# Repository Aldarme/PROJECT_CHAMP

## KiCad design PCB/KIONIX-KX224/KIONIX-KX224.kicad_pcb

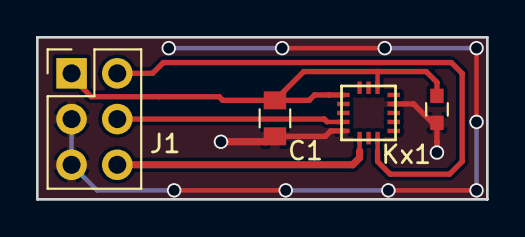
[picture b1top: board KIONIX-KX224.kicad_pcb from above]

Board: 2 copper layers, 25.0 x 9.0 mm, 4 parts (0 on the bottom side), 5 nets.

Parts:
C1: 100nF; C_0805
C2: 100nF; C_0603
J1: Conn_02x03_Odd_Even; Pin_Header_Straight_2x03_Pitch2.54mm
Kx1: KX224

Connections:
/CS/SCL: J1.2, Kx1.8
/Miso/Mosi: J1.6, Kx1.6
/SCLK: J1.4, Kx1.4
/VDD: C1.1, C2.1, J1.1, Kx1.1, Kx1.14
GNDREF: C1.2, C2.2, J1.3, J1.5, Kx1.5, Kx1.12

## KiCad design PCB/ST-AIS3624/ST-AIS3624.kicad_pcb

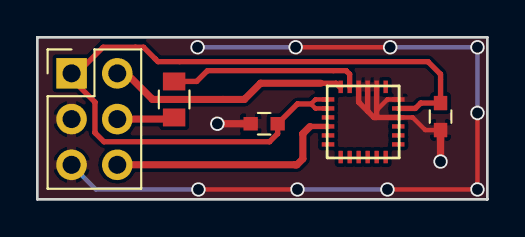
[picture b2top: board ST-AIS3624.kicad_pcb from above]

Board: 2 copper layers, 25.0 x 9.0 mm, 5 parts (0 on the bottom side), 6 nets.

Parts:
AIS36241: AIS3624DQTR; ADIS3624DQ
C1: 100nF; C_0603
C2: 10uF; C_0603
J1: Conn_02x03_Odd_Even; Pin_Header_Straight_2x03_Pitch2.54mm
JP2: Jumper; C_0805

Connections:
/CS/SCL: AIS36241.12, J1.2
/Miso/Mosi: AIS36241.16, J1.6
/SCLK: AIS36241.11, JP2.2
/VDD: AIS36241.5, AIS36241.13, AIS36241.14, C1.1, C2.1, J1.1
GNDREF: AIS36241.4, AIS36241.6, AIS36241.8, AIS36241.9, AIS36241.10, C1.2, C2.2, J1.3, J1.5
unnamed: J1.4, JP2.1

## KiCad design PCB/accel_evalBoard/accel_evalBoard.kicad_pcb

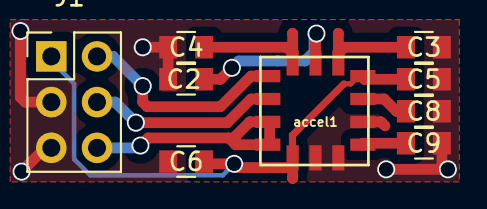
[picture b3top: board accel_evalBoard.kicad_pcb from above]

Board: 2 copper layers, 9 parts (0 on the bottom side), 10 nets.

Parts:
C2, C3, C4, C5, C6, C8, C9: 0.1uF; C_0805
J1: Conn_02x03_Odd_Even; Pin_Header_Straight_2x03_Pitch2.54mm
accel1: ADXL355

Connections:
GNDREF: C2.2, C3.2, C4.2, C5.2, C6.1, C8.1, C9.1, J1.3, J1.5, accel1.6, accel1.7, accel1.9
unnamed: C2.1, accel1.13
unnamed: C3.1, accel1.12
unnamed: C4.1, accel1.14
unnamed: C8.2, accel1.10
unnamed: C9.2, accel1.8
unnamed: J1.2, accel1.1
unnamed: J1.4, accel1.2
unnamed: J1.6, accel1.3, accel1.4
VDD: C5.1, C6.2, J1.1, accel1.5, accel1.11

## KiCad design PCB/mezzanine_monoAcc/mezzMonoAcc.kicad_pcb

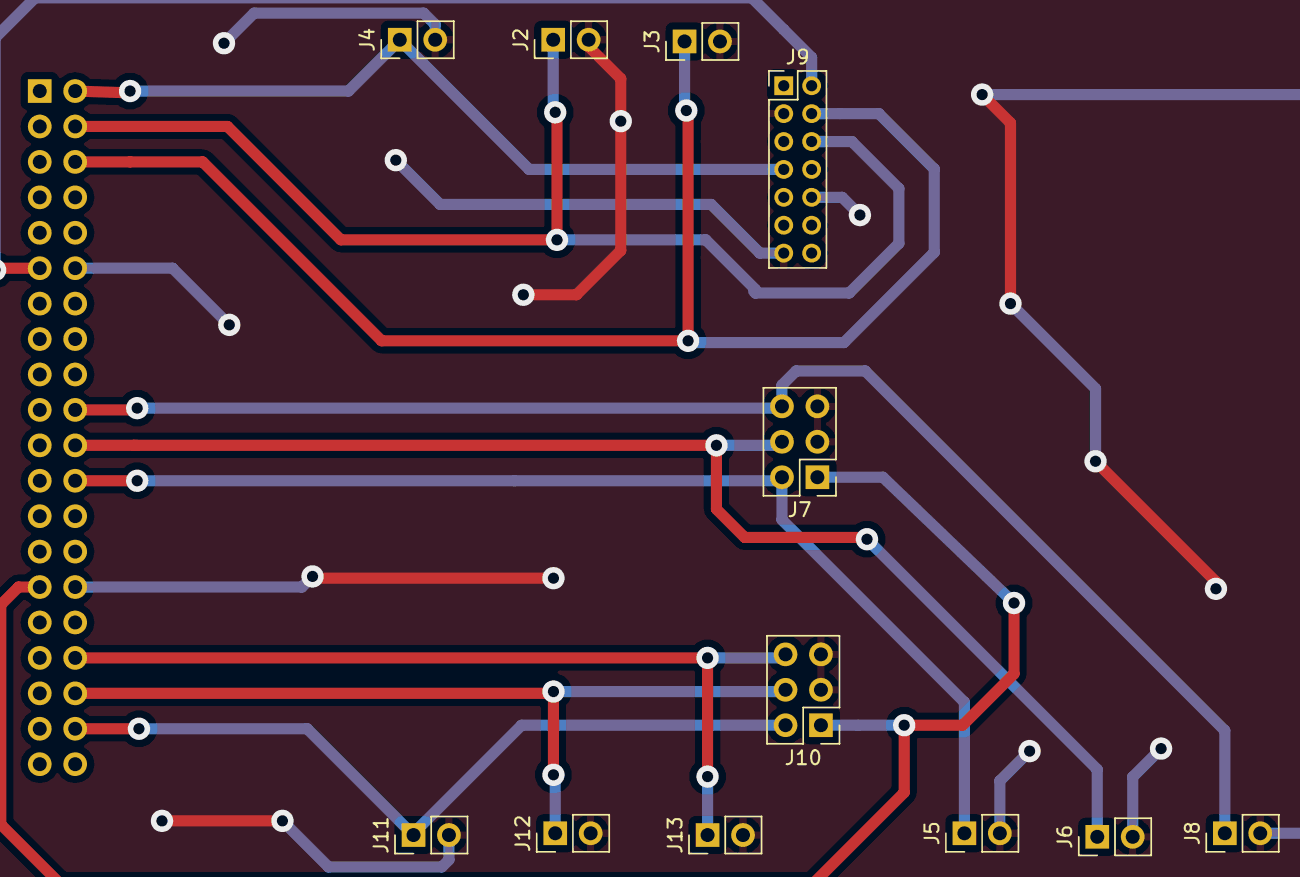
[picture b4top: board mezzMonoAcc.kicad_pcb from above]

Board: 2 copper layers, 13 parts (1 on the bottom side), 12 nets.

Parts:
J1: Conn_02x20_Odd_Even; Socket_Strip_Straight_2x20_Pitch2.54mm
J2, J3, J4, J5, J6, J8, J11, J12, J13: Conn_01x02; Pin_Header_Straight_1x02_Pitch2.54mm
J7, J10: Conn_02x03_Odd_Even; Pin_Header_Straight_2x03_Pitch2.54mm
J9: Conn_02x07_Odd_Even; Pin_Header_Straight_2x07_Pitch2.00mm

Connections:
/ACC_CLK_1: J1.22, J6.1, J7.4
/ACC_CLK_2: J1.36, J10.4, J12.1
/ACC_CS_1: J1.24, J5.1, J7.2
/ACC_CS_2: J1.38, J10.2, J11.1
/ACC_MI/MO_1: J1.20, J7.6, J8.1
/ACC_MI/MO_2: J1.34, J10.6, J13.1
/DAC_CLK: J1.6, J3.1, J9.4
/DAC_CS: J1.4, J2.1, J9.6
/DAC_MISO: J1.2, J4.1, J9.7
/VDD(3.3V): J1.29, J7.1, J10.1
/VDD(5V): J1.11, J9.2
GNDREF: J1.12, J1.30, J2.2, J3.2, J4.2, J5.2, J6.2, J7.3, J7.5, J8.2, J9.3, J9.10, J9.13, J10.3, J10.5, J11.2, J12.2, J13.2

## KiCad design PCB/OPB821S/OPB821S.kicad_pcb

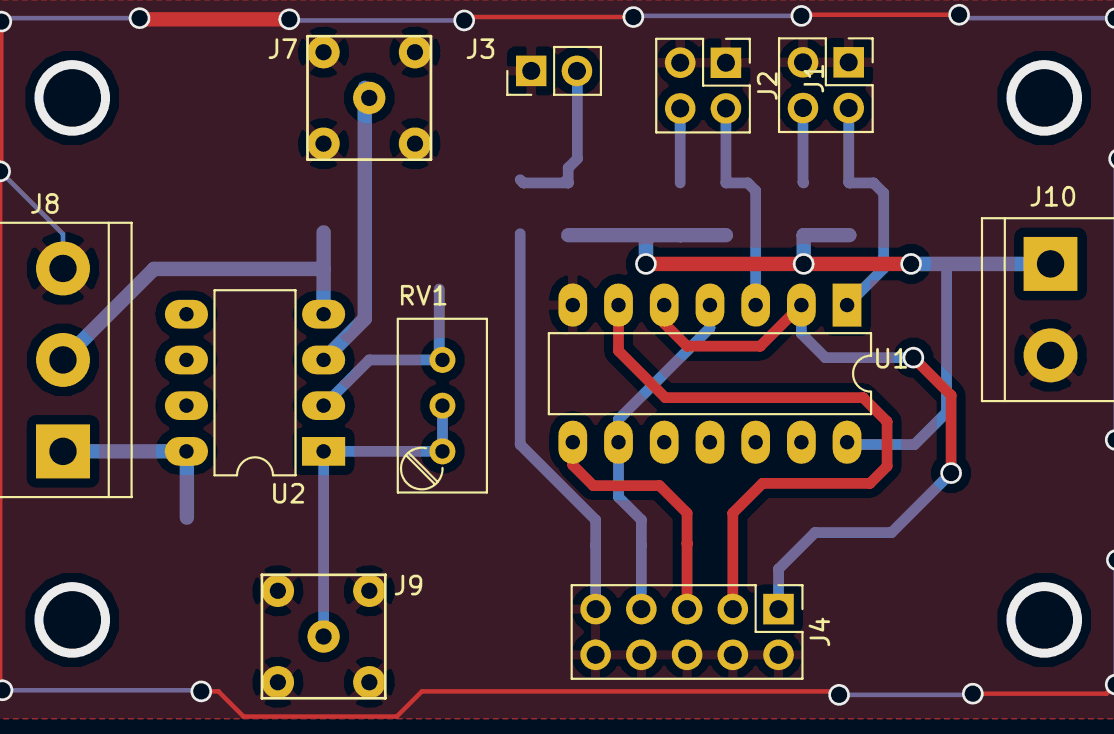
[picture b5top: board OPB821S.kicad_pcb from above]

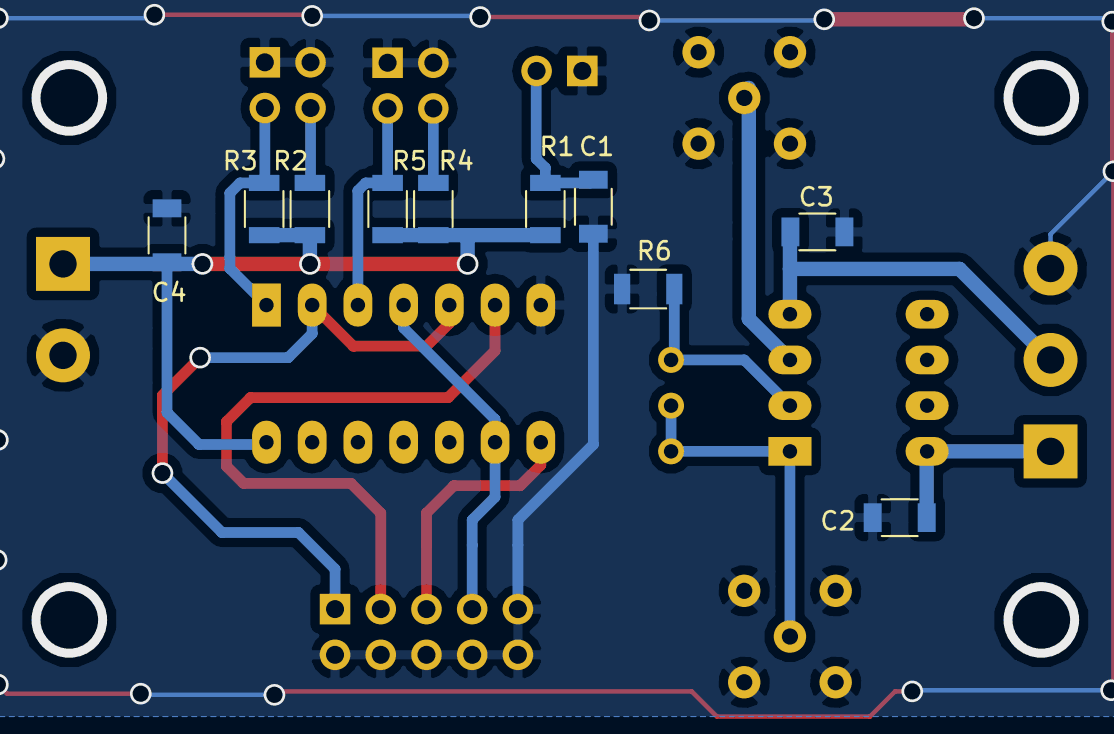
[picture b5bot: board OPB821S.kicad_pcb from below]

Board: 2 copper layers, 21 parts (10 on the bottom side), 16 nets.

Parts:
C1, C2, C3, C4: 100nF; C_1206
J1, J2: Conn_02x02; Pin_Header_Straight_2x02_Pitch2.54mm
J3: Conn_01x02; Pin_Header_Straight_1x02_Pitch2.54mm
J4: Conn_02x05_Odd_Even; Pin_Header_Straight_2x05_Pitch2.54mm
J7, J9: LEMO5; LEMO_footprint
J8: Screw_Terminal_01x03; TerminalBlock_bornier-3_P5.08mm
J10: Screw_Terminal_01x02; TerminalBlock_bornier-2_P5.08mm
R1, R2, R4, R6: 10K; R_1206
R3, R5: 100; R_1206
RV1: 10k - 50k; Potentiometer_Trimmer_Bourns_3296W
U1: 74HC14; DIP-14_W7.62mm_LongPads
U2: OP249; DIP-8_W7.62mm_LongPads

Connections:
/Vm: C3.1, J8.2, U2.4
/Vp: C2.1, J8.1, U2.8
GND: C1.2, C2.2, C3.2, C4.2, J1.1, J1.3, J2.1, J2.3, J3.1, J4.2, J4.4, J4.6, J4.8, J4.9, J4.10, J7.2, J7.3, J7.4, J7.5, J8.3, J9.2, J9.3, J9.4, J9.5, J10.2, R6.2, U1.7
unnamed: C1.1, J3.2, R1.1
unnamed: J1.2, R3.2, U1.1
unnamed: J1.4, R2.2
unnamed: J2.2, R5.2, U1.3
unnamed: J2.4, R4.2
unnamed: J4.1, U1.2, U1.5
unnamed: J4.3, U1.6
unnamed: J4.5, U1.8
unnamed: J4.7, U1.4, U1.9
unnamed: J7.1, U2.3
unnamed: J9.1, RV1.1, RV1.2, U2.1
unnamed: R6.1, RV1.3, U2.2
VCC: C4.1, J10.1, R1.2, R2.1, R3.1, R4.1, R5.1, U1.14

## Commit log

2018-02-14 ADD administratif ST50 doc & Datasheets
2018-02-14 add sources folder
2018-02-15 "test_accel" modify for ADXL355
2018-02-15 Adapte "test_accel" for multiSensor
2018-02-15 Add documents
2018-02-15 Update files
2018-02-15 Create stub for ADXL355 && Adapt testBench
2018-02-16 redefine range of Redled used && set SPIFREQ at 10Mhz
2018-02-19 report documents && administratif doc
2018-02-19 Doc asservissemment
2018-02-19 Report documents
2018-02-19 Use "generate" to have a mecanisme of instantition, as P2O
2018-02-21 Add documentations
2018-02-21 Debug SPI MASTER when SS = 1 -> SCLOCK = 0
2018-02-21 add updated modification into licence controle
2018-02-21 implementation of the good protocol to configure accelero
2018-02-21 access accelero register to read the 20 bits of Zaxis
2018-02-22 add DAC documentation
2018-02-27 add DE115 manualuser
2018-02-27 Hack 4 wire SPI into a 3 wire SPI
2018-02-27 FIX BUG - SPI 3 wires register configuration
2018-03-01 update code to use muti-architecture
2018-03-01 add spi_DAC file
2018-03-02 update code
2018-03-02 Create top entity to control ACCEL & FILTER & DAC
2018-03-02 create Filter entity
2018-03-03 Repport : Project presentation Ended
2018-03-03 update repport
2018-03-05 Compile module, composed of : SPI_ACCEL & Filter & SPI_dac
2018-03-05 add topEntity testbench to deploy simulation
2018-03-07 PCB for accel evalBoard
2018-03-07 PCB png for report
2018-03-09 photo_PCB_2.3
2018-03-09 Add PCB 2.3
2018-03-09 AOP for generator signal
2018-03-09 update and debug
2018-03-16 add simulation of DAC LTC2668-16
2018-03-16 minor update
2018-03-16 update SPI_DAC to perform format: 16 bits input && 24 bits output
2018-03-27 EvalBoard for test with OPB821S & OP
2018-03-27 VHDL - ADD FILFO for SPI DAC
2018-03-27 VHDL - ADD DAC emulation
2018-03-27 DAC debug ended
2018-03-28 elements deleted
2018-03-28 evalBoard ended - docs produce for report
2018-03-28 OPB board ended - docs produce for report
2018-03-29 add last document & convert line in class 4
2018-03-29 add last doc & convert line in class 4
2018-03-30 Fix clock Bug
2018-03-30 Add simu docs
2018-04-03 add oscillo_chrono_pict
2018-04-03 add .sof file (register of exec)
2018-04-03 update code GPIO input in sub module for futur "generate" feature
2018-04-06 add new TOP created for generate
2018-04-06 add filter file to adapte to generate
2018-04-06 add new SPI8DAC to adapte to generate archi
2018-04-06 update mono module to use only concerned GPIO per Composants
2018-04-06 add generic var
2018-04-06 unsed files
2018-04-09 create test bench for GenerateEntity
2018-04-09 update modif
2018-04-18 add clockDivider to have a smaller work frequency
2018-04-24 fix error for photoContactor connexion
2018-04-25 Update ground plan & connexion to accel
2018-04-27 last exec of success working module
2018-04-27 add ASYNCH FIFO
2018-04-27 update concat registers on 24 bits word
2018-04-27 fix bug on FIFO
2018-04-27 last exec of fonctionnel module
2018-04-27 add NO gate datasheet
2018-05-02 Update - prototype tested and fonctional
2018-05-02 integrate guard ring into the ground plane
2018-05-02 add accel config for HPF with cutoff frequency of 0.238 * ODR (1Khz)
2018-05-02 rescale data to have 8g -> 10v, 1g -> 1.25v
2018-05-03 concatene z data register into a 20 bits word and update to allow modif
2018-05-03 In 1 clock event read and flush acquitement
2018-05-04 add USB document & .sof file
2018-05-04 update PCB eval board
2018-05-09 RS232 communication for DE2-115
2018-05-10 Report: "projet et thématique" finished
2018-05-10 add plan projet
2018-05-11 uart Tx and Rx finished
2018-05-11 add author of documents
2018-05-11 add rs232 transceiver to transmit data
2018-05-14 update evalBoard_2.3 docs
2018-05-16 lastUpdate
2018-05-18 update - soustract g & rescale 20 bit into 16 bits data
2018-05-18 add accélération representation data
2018-05-18 modif archi to fit 20 bit data of accéléro
2018-05-22 Acc - implement acces control to the NVM to read dataZ
2018-05-22 filter-implement multiArch for test bench
2018-05-24 New PCB - Mezza mono Acc
2018-05-24 minor update for PCB
2018-05-25 fix error pin assignment - 5v DAC pin2
2018-05-25 docs pcb mezza - wiring map with drilling hole
2018-05-25 filter - add DAC "gain" control by switch
2018-05-25 ST50 Docs - add imgs of FPGA to DAC && DAC repons
2018-05-28 filter - add 7segmt to display signal's divisor
2018-05-29 filter - search to have pos & neg value
2018-05-29 any update
2018-05-31 filter - filter_mapBit allow to have signal from -8g to +8g
2018-06-01 filter - update bitMap function with signal division (arti gain for ADC)
2018-06-01 accel - add time between of conf. register (~180 us)
2018-06-05 Faulhaber pressBook
2018-06-05 add IP_FIFO
2018-06-05 spi_dac - used new IP_FIFO to avoid metastability
2018-06-05 update .sof & .pof file
2018-06-21 signal bruité - métastabilité
2018-06-21 graph pour établissement de la function de transfère
2018-06-22 add info parametrage oscillo
2018-06-22 Asservissement - Analysis & data
2018-06-22 Filter - add integration signal to obtain speed and position from signal
2018-07-01 report - ended previsionnel & effective work
2018-07-01 report - gant resume in "portrait"
2018-07-01 report - Gant update file harchi
2018-07-01 report - ingration of "planning" and related pdf files
2018-07-01 report - add ST50_ROMETPierre.pdf file to gitignore
2018-07-05 3D_print accelerometer support for piano.
    This support is a first proto, used for technical tests. a new one will be prepare in case of trubble with gaming experience.
2018-07-05 Asservissement - doc to establish transfert function
2018-07-09 report - add "tableoffigure" and give number to each figure
2018-07-09 ST50 - fiche de suivis de dernière semaine
2018-07-09 report - finis correctement l'image CH.png
2018-07-09 report - update plan
2018-07-09 report - correct some trubble ready to start work description
2018-07-10 report - begin first manip
2018-07-10 report - add schema bloc for manip 1&2
2018-07-10 report - 1er manip finie
2018-07-10 report - traitement du signal finie
2018-07-11 report - 1ère passage correction orthographe
2018-07-11 report - refonte de la présentation des expérience mené par le labos
2018-07-12 Document de prise en main de l'arbo du projet
2018-07-12 Détail avant fin stage
2018-07-12 Doc prise en main arbo projet
2018-07-23 report - TODO "hack" SPI bus
2018-07-25 Report - Annexe to finished
2018-07-26 report - ended - 1st corection done & page setting done
2018-07-27 report - first orthograph pass
2018-07-31 report - ortho ended
2018-08-09 report - update "Hack protocol SPI" with good practice for manip
2018-09-04 Presentation part
2018-09-05 Presentation - final version
2018-09-10 Presentation - PDF&Windows version
2018-09-10 documentation - new accelerometers
2018-09-12 Docs - New datasheet for new accelero
2018-09-12 filter - new algo for sldding avrg && new state mach for integ acc&speed
2018-09-17 filter-define a dedicate acceleration-average process
2018-09-17 revision-define a dedicate process for acc,avrg,speed,pos
2018-09-24 FIFO-24 new fifo deep: 1024 & word of 24 bits
2018-09-24 ASP-files modified & ready for simu
2018-09-24 ASP-add tb file for simulation (debug version)
2018-09-24 ASP-update files name to allow modelsim to differentiate files
2018-09-26 FIFO-24 - update IP model to have acces to the nbr of word into the fifo
2018-09-26 ASP-add a stub model of testBench to simulate SPI_DAC
2018-09-26 ASP-testBench modif & updated code thank to simu&debug
2018-10-02 FIFO-24 update model to optimise access time
2018-10-02 ASP-fix bug - structural bug with multiple access to a structure
2018-10-02 ASP-update global test bench
2018-10-02 ST-create projet for AIS3624 new pcb
2018-10-09 docs - complete data sheet of AIS3624
2018-10-09 PCB-add layout & pcb for AIS3624
2018-10-09 PCB - accel_evalboard delete internal librarie
2018-10-09 PCB - OPB delete internal librarie
2018-10-09 PCB - create a mutialized librairie for components & footprint
2018-10-10 PCB - stag new accelerometer KIONIX KX224
2018-10-10 PCB - update KX224
2018-10-22 PCB - Kionix v 1.5, ready to print
2018-10-22 PCB - ST-AIS v 1.5, ready to print
2018-10-23 docs - configuration file for accelerometer registers
2018-10-23 docs - switch "ETAT de l'art" file to uncrypted file
2018-10-23 docs - configuration file, fix mistake
2018-10-24 PCB - AIS3624 update after review with meca staff
2018-10-24 PCB - KX224 update after review with meca staff
2018-10-24 PCB - KX224 fix via wiring mistake
2018-10-24 PCB - KX224 update & manufacturing files
2018-10-24 PCB - Update of the library of components
2018-10-24 PCB - KX224 little modif
2018-10-25 PCB - KX224 update to have file conform to manufacturate PCB
2018-10-29 Docs - Kx224 add archive controle pcb
2018-10-29 Docs - AIS3624 add archive controle pcb & minor update
2018-10-29 Docs - ADXL355 add archive controle pcb & minor update
2018-10-29 Docs - add globale archive controle PCB file
2018-10-30 Docs - administrative doc to command PCBs
2018-10-30 ASP - update SPI_master to be RW adaptative to diff word Lenght
2018-10-30 ASP - compile version of "ASP_spi_master_Rw_adaptative_wordLenght"
2018-10-30 ASP - spi_accel major maj, impl SPI_adapt & arch config for diff accs
2018-10-31 ASP - write KX224 behavior to test his SPI protocole
2018-11-05 ASP - specify folder for TESTBENCH
2018-11-05 ASP - testBench for KX224
2018-11-05 ASP - KX beh fix little bugs
2018-11-05 ASP - fix fatal error in nbr of write bit into "transmit to slave"
2018-11-05 Docs - fix mistake into hex value to set ODR at 1600Hz
2018-11-06 ASP - spi_master implmt auto-config accding to accel used & delete latch
2018-11-06 ASP - SPI_ACCEL implmt spi_read_freq auto-conf & VHDL 2008 generate arch
2018-11-06 PCB - KX224 add missing "drill files"
2018-11-12 PCB-AIS3624 v2.0 verified
2018-11-12 Docs - docs for AIS3624 v2.0 update
2018-11-12 Docs - AIS3624 update liste composant
2018-11-12 PCB - KX224 V2.0 verified
2018-11-12 Docs - docs for KX224 v2.0 Update
2018-11-13 ASP - functional avrg acceleration
2018-11-16 Docs - update register configuration for accelerometers
2018-11-16 Docs - update AIS3624 F.CU to fiw bad wiring
2018-11-16 PCB - AIS3624 fix bad wiring for SPI interface 3-wire
2018-11-16 ASP - SPI-DAC fix unstable parameter
2018-11-16 ASP - Filter Speed & position zero at rest -OK need to dev a fctio adder
2018-11-21 ASP - spi master comment modif
2018-11-21 ASP - DAC major maj - optimize resynchro register, R/W fifo, SPI Read
2018-11-21 ASP - Accel&Top add header file
2018-11-23 docs - add new data into acceleration info
2018-11-23 ASP - v2 of accspedpos test bench
2018-11-23 ASP - new avrg method to dev
2018-11-26 Docs - excel accel file
2018-11-26 ASP - filter integrate speed & pos - still cnt bug to fix
2018-11-27 PCB - kionix, fix pin wiring mistake
2018-11-27 ASP - filter - Functional
2018-11-28 Docs - add paper docs & latest development
2018-11-28 ASP - filter spd&pos integrator simu:OK; in real: diverge
2018-11-28 Docs - Range G - signed - unsigned
2018-11-28 ASP_filter spd&pos integ. functional
2018-11-28 Docs - add methodology of acc&speed integration
2018-11-29 ASP - oe_motor sur GPIO & integ speed stop after hit & calib spd&pos
2018-11-29 Docs - champ description
2018-11-29 ASP - Calibration en vitesse & position validé avec antoine
